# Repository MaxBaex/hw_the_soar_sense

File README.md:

# PCB design for sense module
Minimalistic very small temperature and humidity sensing device with CAN interface. Could also be used for other CAN bus attached sensing tasks. 

## Facts
- SWD interface
- STM32F103 48LQFP 8 MHz Crystal 
- CAN transceiver: MAX3051EKA+T 
- 5 to 16V power supply with 3.3V LDO: SPX3819M5-L-3-3/TR
- Temperature and Humidity sensing with SHT35-DIS-B or SHT31
- 4 analog inputs, SPI, 2 I2C and UART 
- Boot0 pin available for flashing via UART
- Pcb size 47.7mm x 23.2mm

## 3D Preview 

## TODO
- backside solder pads for differential pressure package 
- more backside connectors 
- review and feedback
- are the cable solder connections the right choice?
- make sensor voltage switchable! 
- add some signal leds

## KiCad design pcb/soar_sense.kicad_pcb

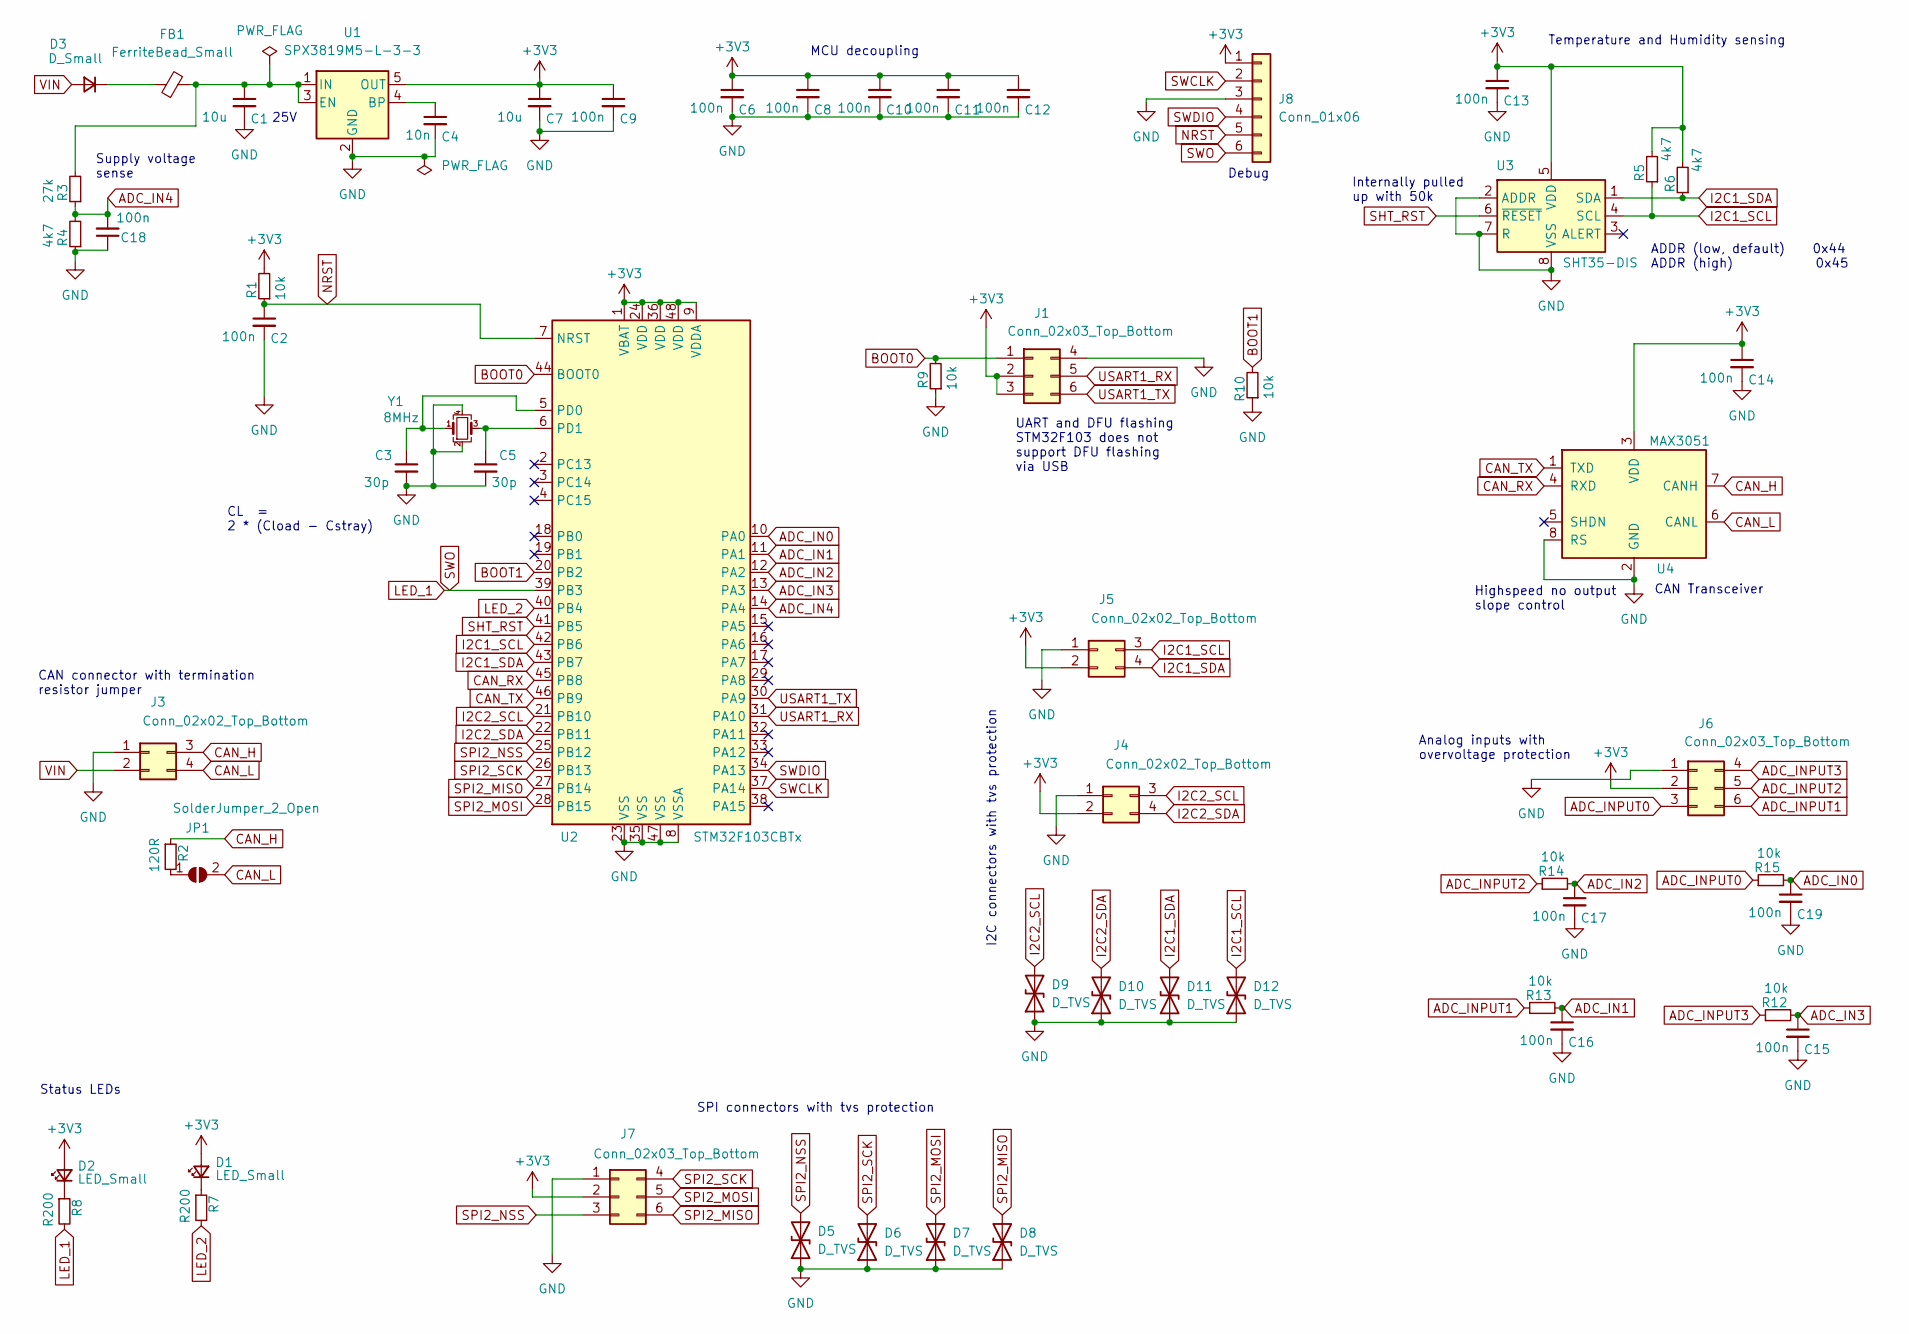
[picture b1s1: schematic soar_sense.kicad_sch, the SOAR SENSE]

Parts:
C1: 10u; C_0603_1608Metric; LCSC Part Number C91606
C2, C6, C8, C9, C10, C11, C12, C13, C14, C15, C16, C17, C18, C19: 100n; C_0603_1608Metric; LCSC Part Number C14663
C3, C5: 30p; C_0402_1005Metric; LCSC Part Number C1570
C4: 10n; C_0603_1608Metric; LCSC Part Number C57112
C7: 10u; C_0603_1608Metric; LCSC Part Number C19702
D1, D2: LED_Small; D_0603_1608Metric; LCSC Part Number C72041
D3: D_Small; D_SOD-323; LCSC Part Number C22624
D5, D6, D7, D8, D9, D10, D11, D12: D_TVS; D_SOD-323; LCSC Part Number C51450
FB1: FerriteBead_Small; L_0805_2012Metric; LCSC Part Number C1017
J1, J6, J7: Conn_02x03_Top_Bottom; pcb_edge_2_3
J3, J4, J5: Conn_02x02_Top_Bottom; pcb_edge_2_2
J8: Conn_01x06; Molex_PicoBlade_53048-0610_1x06_P1.25mm_Horizontal
JP1: SolderJumper_2_Open; SolderJumper-2_P1.3mm_Open_Pad1.0x1.5mm
R1, R9, R10, R12, R13, R14, R15: 10k; R_0603_1608Metric; LCSC Part Number C25804
R2: 120R; R_0603_1608Metric; LCSC Part Number C22787
R3: 27k; R_0603_1608Metric; LCSC Part Number C22967
R4, R5, R6: 4k7; R_0603_1608Metric; LCSC Part Number C23162
R7, R8: R200; R_0603_1608Metric; LCSC Part Number C8218
U1: SPX3819M5-L-3-3; SOT-23-5; LCSC Part Number C9055
U2: STM32F103CBTx; LQFP-48_7x7mm_P0.5mm; LCSC Part Number C8304
U3: SHT35-DIS; Sensirion_DFN-8-1EP_2.5x2.5mm_P0.5mm_EP1.1x1.7mm; LCSC Part Number C90161
U4: MAX3051; SOT-23-8_Handsoldering; LCSC Part Number C112005
Y1: 8MHz; Crystal_SMD_5032-4Pin_5.0x3.2mm; LCSC Part Number C157341

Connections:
+3V3: C6.1, C7.1, C8.1, C9.1, C10.1, C11.1, C12.1, C13.1, C14.1, D1.2 (A), D2.2 (A), J1.2, J1.3, J4.2, J5.2, J6.2, J7.2, J8.1, R1.2, R5.2, R6.2, U1.5 (OUT), U2.1 (VBAT), U2.9 (VDDA), U2.24 (VDD), U2.36 (VDD), U2.48 (VDD), U3.5 (VDD), U4.3 (VDD)
ADC_IN0: C19.1, R15.2, U2.10 (PA0)
ADC_IN1: C16.1, R13.2, U2.11 (PA1)
ADC_IN2: C17.1, R14.2, U2.12 (PA2)
ADC_IN3: C15.1, R12.2, U2.13 (PA3)
ADC_IN4: C18.2, R3.1, R4.2, U2.14 (PA4)
ADC_INPUT0: J6.3, R15.1
ADC_INPUT1: J6.6, R13.1
ADC_INPUT2: J6.5, R14.1
ADC_INPUT3: J6.4, R12.1
BOOT0: J1.1, R9.2, U2.44 (BOOT0)
BOOT1: R10.2, U2.20 (PB2)
CAN_H: J3.3, R2.1, U4.7 (CANH)
CAN_L: J3.4, JP1.2 (B), U4.6 (CANL)
CAN_RX: U2.45 (PB8), U4.4 (RXD)
CAN_TX: U2.46 (PB9), U4.1 (TXD)
GND: C1.2, C2.2, C3.2, C4.2, C5.2, C6.2, C7.2, C8.2, C9.2, C10.2, C11.2, C12.2, C13.2, C14.2, C15.2, C16.2, C17.2, C18.1, C19.2, D5.1 (A1), D6.1 (A1), D7.1 (A1), D8.1 (A1), D9.1 (A1), D10.1 (A1), D11.1 (A1), D12.1 (A1), J1.4, J3.1, J4.1, J5.1, J6.1, J7.1, J8.3, R4.1, R9.1, R10.1, U1.2 (GND), U2.8 (VSSA), U2.23 (VSS), U2.35 (VSS), U2.47 (VSS), U3.2 (ADDR), U3.7 (R), U3.8 (VSS), U3.9 (VSS), U4.2 (GND), U4.8 (RS), Y1.2, Y1.4
I2C1_SCL: D12.2 (A2), J5.3, R5.1, U2.42 (PB6), U3.4 (SCL)
I2C1_SDA: D11.2 (A2), J5.4, R6.1, U2.43 (PB7), U3.1 (SDA)
I2C2_SCL: D9.2 (A2), J4.3, U2.21 (PB10)
I2C2_SDA: D10.2 (A2), J4.4, U2.22 (PB11)
LED_1: J8.6, R8.2, U2.39 (PB3)
LED_2: R7.2, U2.40 (PB4)
NRST: C2.1, J8.5, R1.1, U2.7 (NRST)
unnamed: C1.1, FB1.2, R3.2, U1.1 (IN), U1.3 (EN)
unnamed: C3.1, U2.5 (PD0), Y1.1
unnamed: C4.1, U1.4 (BP)
unnamed: C5.1, U2.6 (PD1), Y1.3
unnamed: D1.1 (K), R7.1
unnamed: D2.1 (K), R8.1
unnamed: D3.1 (K), FB1.1
unnamed: JP1.1 (A), R2.2
SHT_RST: U2.41 (PB5), U3.6 (~RESET)
SPI2_MISO: D8.2 (A2), J7.6, U2.27 (PB14)
SPI2_MOSI: D7.2 (A2), J7.5, U2.28 (PB15)
SPI2_NSS: D5.2 (A2), J7.3, U2.25 (PB12)
SPI2_SCK: D6.2 (A2), J7.4, U2.26 (PB13)
SWCLK: J8.2, U2.37 (PA14)
SWDIO: J8.4, U2.34 (PA13)
USART1_RX: J1.5, U2.31 (PA10)
USART1_TX: J1.6, U2.30 (PA9)
VIN: D3.2 (A), J3.2

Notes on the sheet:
Supply voltage sense
MCU decoupling
CAN connector with termination resistor jumper
I2C connectors with tvs protection
25V
ADDR (low, default) 0x44 ADDR (high) 0x45
Temperature and Humidity sensing
Internally pulled up with 50k
CAN Transceiver
Analog inputs with overvoltage protection
Highspeed no output slope control
Debug
CL = 2 * (Cload - Cstray)
Status LEDs
UART and DFU flashing STM32F103 does not support DFU flashing via USB
SPI connectors with tvs protection

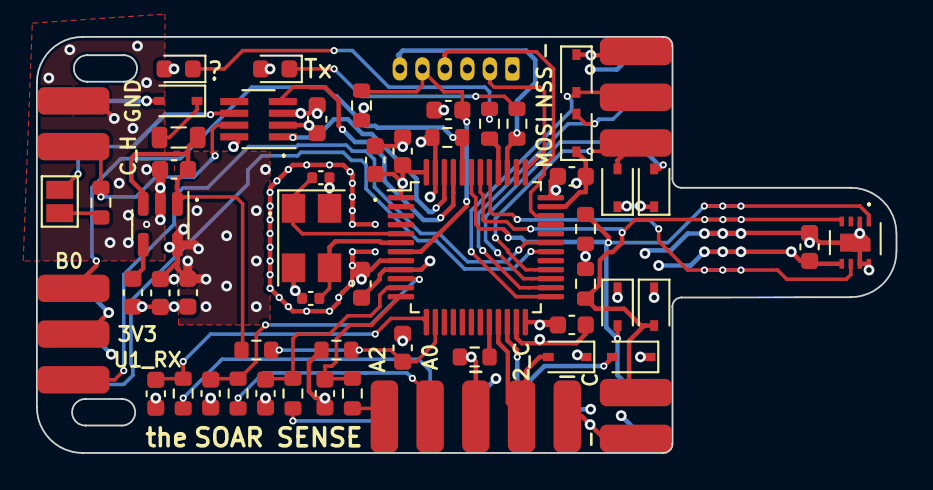
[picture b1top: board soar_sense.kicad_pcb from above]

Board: 4 copper layers, 47.8 x 23.1 mm, 58 parts (1 on the bottom side), 42 nets.

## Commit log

2022-01-09 today done
2022-01-10 added crystal
2022-01-10 sht connected
2022-01-11 added copper heat cooling areas
2022-01-11 added supply voltage sensing
2022-01-11 added holes
2022-01-11 updated documentation
2022-01-11 add size in picture
2022-01-20 added todos
2022-02-12 add todo
2024-09-19 added licence information
